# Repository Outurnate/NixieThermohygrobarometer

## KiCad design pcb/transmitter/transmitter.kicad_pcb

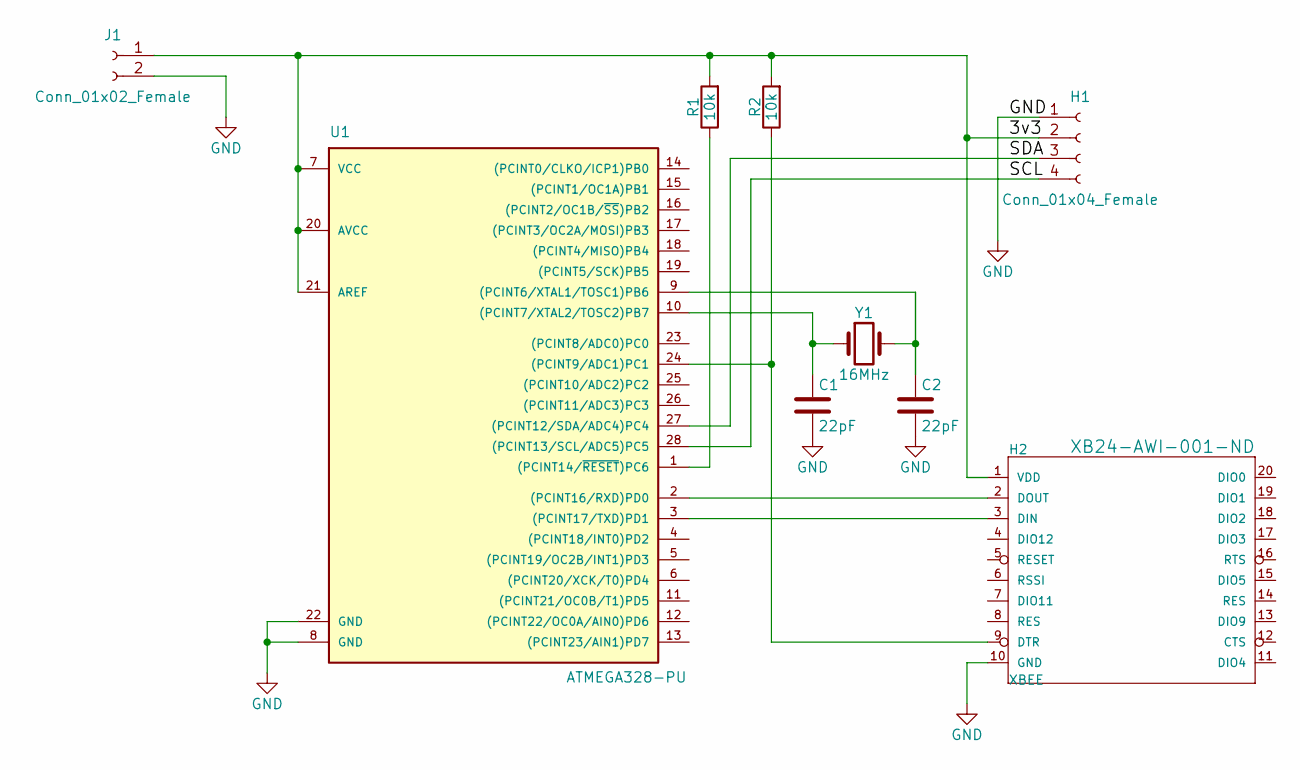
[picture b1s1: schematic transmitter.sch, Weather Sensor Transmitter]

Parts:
C1, C2: 22pF; C_Axial_L5.1mm_D3.1mm_P7.50mm_Horizontal
H1: Conn_01x04_Female; Socket_Strip_Straight_1x04_Pitch2.54mm
H2: XBEE
J1: Conn_01x02_Female; Socket_Strip_Straight_1x02_Pitch2.54mm
R1, R2: 10k; R_Axial_DIN0207_L6.3mm_D2.5mm_P7.62mm_Horizontal
U1: ATMEGA328-PU; DIP28
Y1: 16MHz; Crystal_HC49-U_Vertical

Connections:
/3v3: H1.2, H2.1 (VDD), J1.1, R1.2, R2.2, U1.7 (VCC), U1.20 (AVCC), U1.21 (AREF)
/SCL: H1.4, U1.28 ((PCINT13/SCL/ADC5)PC5)
/SDA: H1.3, U1.27 ((PCINT12/SDA/ADC4)PC4)
GND: C1.2, C2.2, H1.1, H2.10 (GND), J1.2, U1.8 (GND), U1.22 (GND)
unnamed: C1.1, U1.10 ((PCINT7/XTAL2/TOSC2)PB7), Y1.1
unnamed: C2.1, U1.9 ((PCINT6/XTAL1/TOSC1)PB6), Y1.2
unnamed: H2.2 (DOUT), U1.2 ((PCINT16/RXD)PD0)
unnamed: H2.3 (DIN), U1.3 ((PCINT17/TXD)PD1)
unnamed: H2.9 (DTR), R2.1, U1.24 ((PCINT9/ADC1)PC1)
unnamed: R1.1, U1.1 ((PCINT14/~RESET~)PC6)

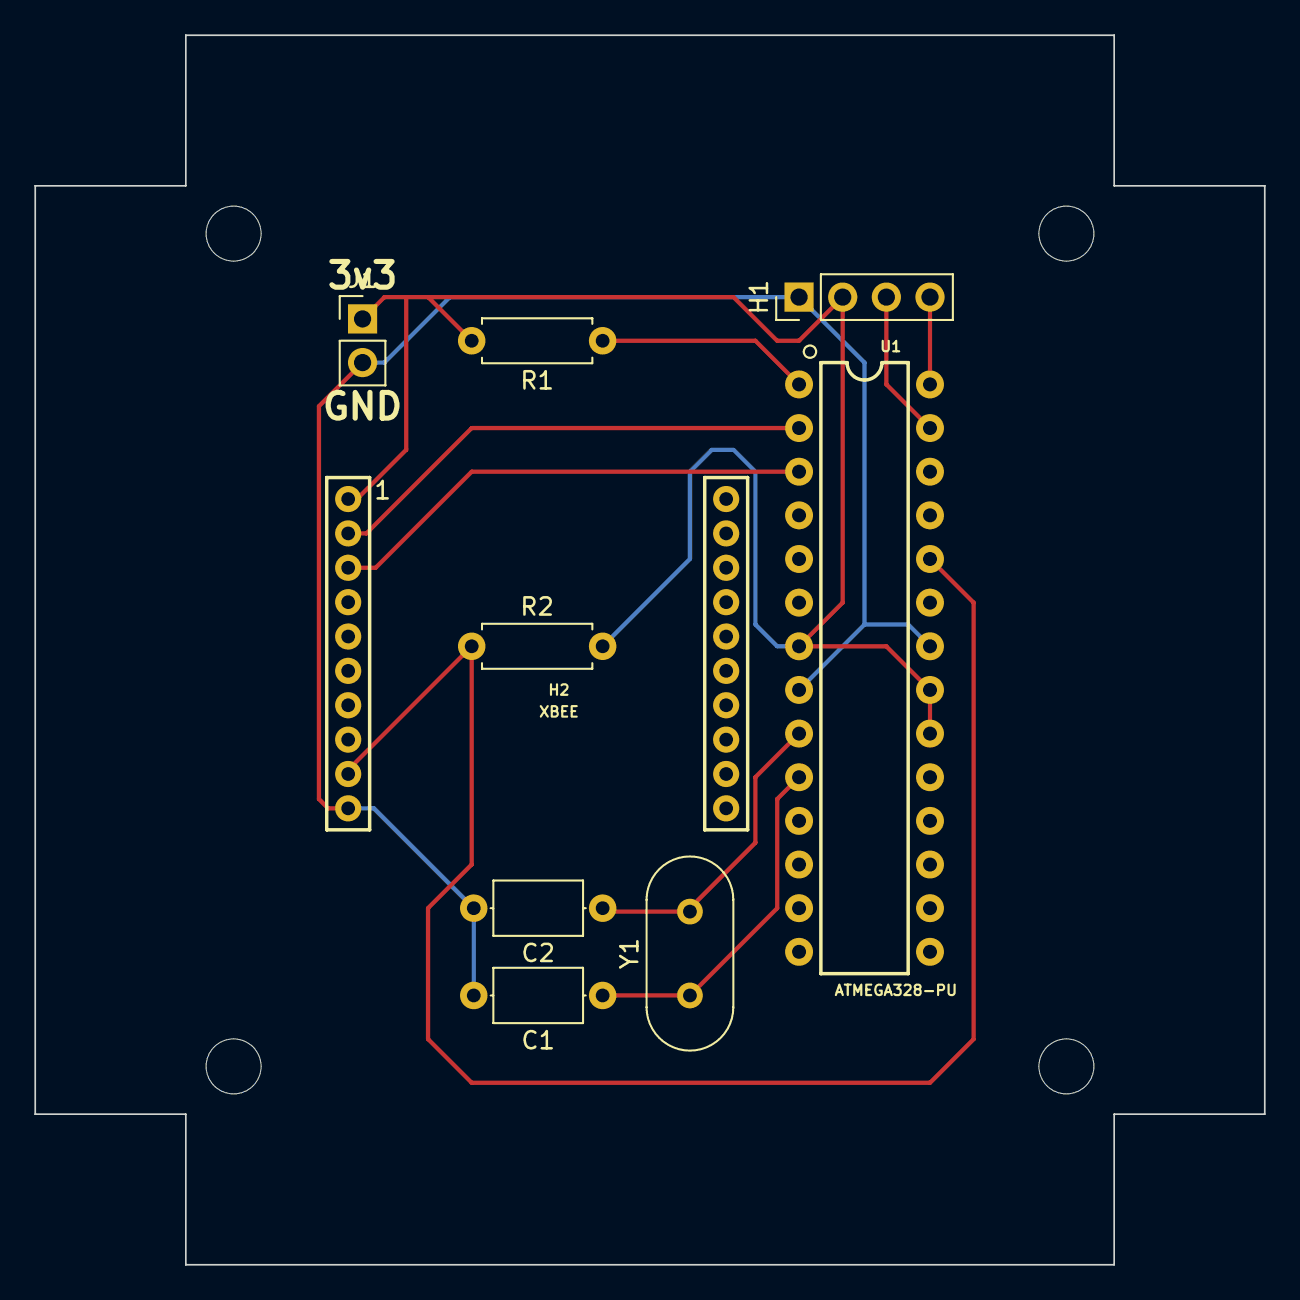
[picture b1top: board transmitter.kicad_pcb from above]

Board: 2 copper layers, 71.6 x 71.6 mm, 9 parts (0 on the bottom side), 10 nets.

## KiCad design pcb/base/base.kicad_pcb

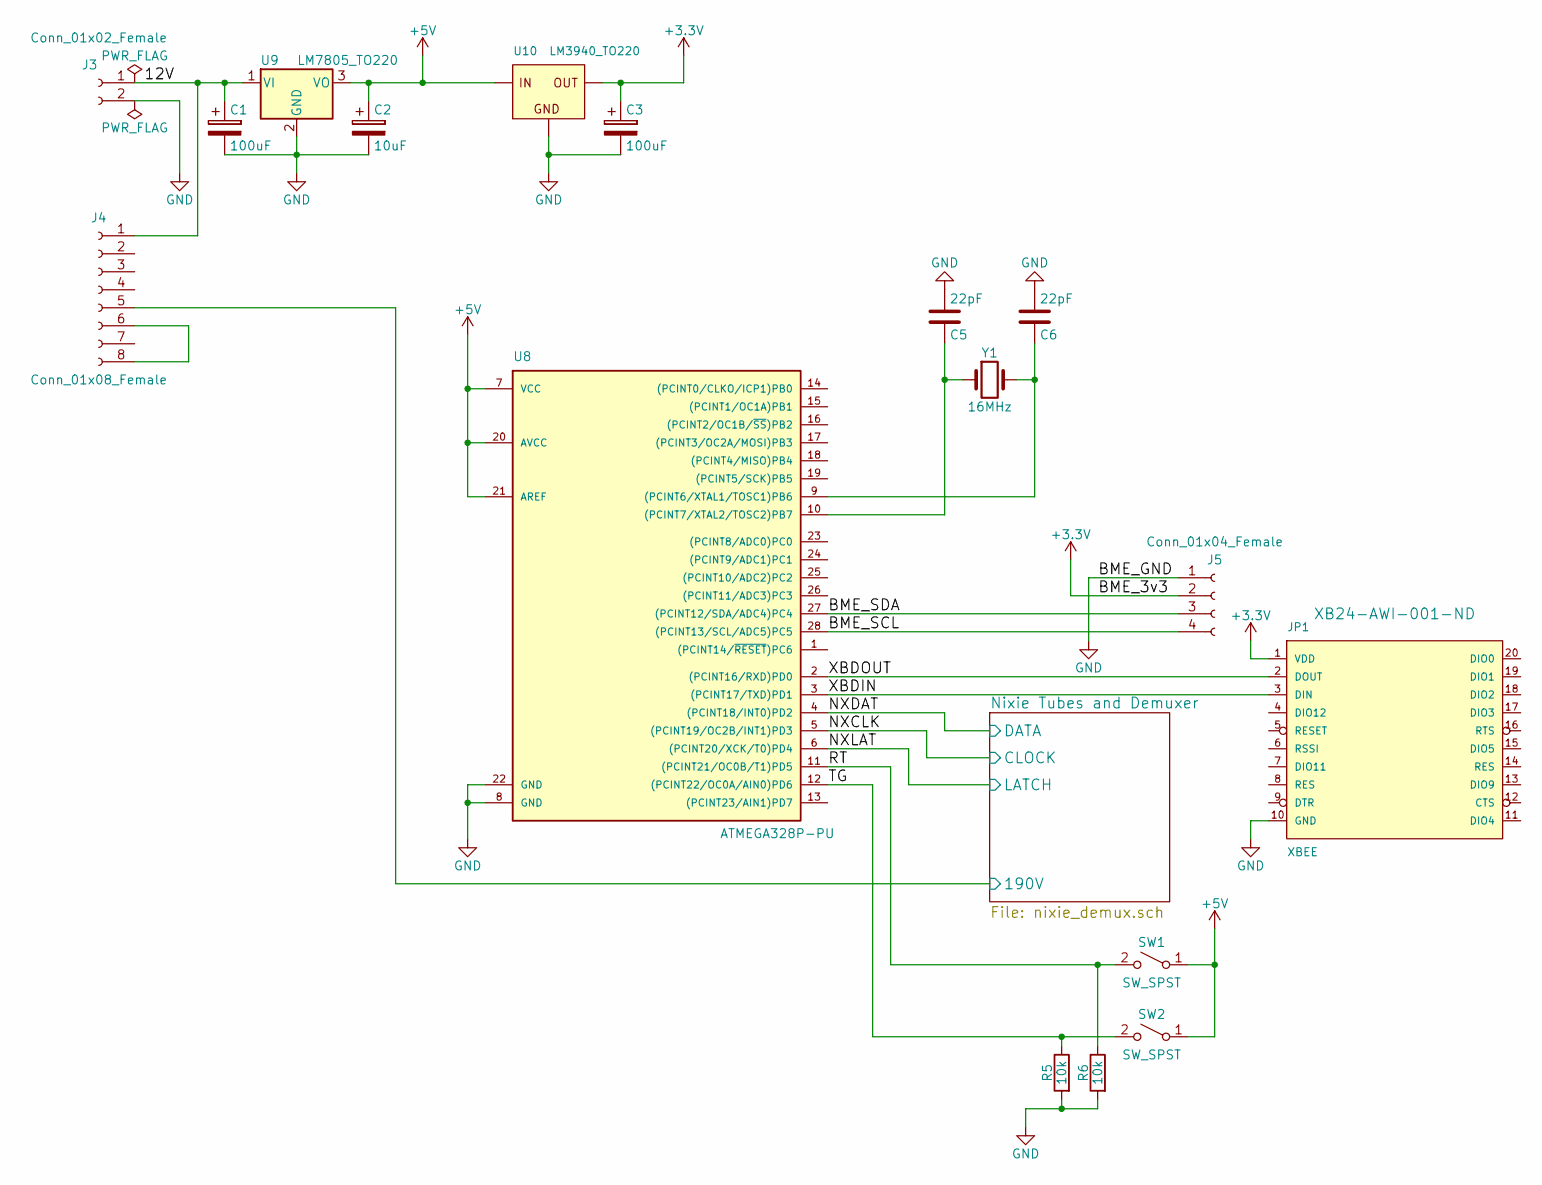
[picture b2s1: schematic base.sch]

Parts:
C1, C3: 100uF; CP_Radial_D6.3mm_P2.50mm
C2: 10uF; CP_Radial_D6.3mm_P2.50mm
C5, C6: 22pF; C_Disc_D4.3mm_W1.9mm_P5.00mm
J3: Conn_01x02_Female; Socket_Strip_Straight_1x02_Pitch2.54mm
J4: Conn_01x08_Female; Socket_Strip_Straight_1x08_Pitch2.54mm
J5: Conn_01x04_Female; Socket_Strip_Straight_1x04_Pitch2.54mm
JP1: XBEE
R5, R6: 10k; R_Axial_DIN0207_L6.3mm_D2.5mm_P7.62mm_Horizontal
SW1, SW2: SW_SPST; Pin_Header_Straight_1x02_Pitch2.54mm
U8: ATMEGA328P-PU; DIP28
U9: LM7805_TO220; TO-220-3_Vertical
U10: LM3940_TO220; TO-220-3_Vertical
Y1: 16MHz; Crystal_HC49-U_Vertical

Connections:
/12V: C1.1, J3.1, J4.1, U9.1 (VI)
/BME_SCL: J5.4, U8.28 ((PCINT13/SCL/ADC5)PC5)
/BME_SDA: J5.3, U8.27 ((PCINT12/SDA/ADC4)PC4)
/NXCLK: U8.5 ((PCINT19/OC2B/INT1)PD3); also elsewhere on the board
/NXDAT: U8.4 ((PCINT18/INT0)PD2); also elsewhere on the board
/NXLAT: U8.6 ((PCINT20/XCK/T0)PD4); also elsewhere on the board
/Nixie Tubes and Demuxer/190V: J4.5; also elsewhere on the board
/RT: R6.1, SW1.2 (B), U8.11 ((PCINT21/OC0B/T1)PD5)
/TG: R5.1, SW2.2 (B), U8.12 ((PCINT22/OC0A/AIN0)PD6)
/XBDIN: JP1.3 (DIN), U8.3 ((PCINT17/TXD)PD1)
/XBDOUT: JP1.2 (DOUT), U8.2 ((PCINT16/RXD)PD0)
GND: C1.2, C2.2, C3.2, C5.2, C6.2, J3.2, J5.1, JP1.10 (GND), R5.2, R6.2, U8.8 (GND), U8.22 (GND), U9.2 (GND), U10.2 (GND); also elsewhere on the board
unnamed: C5.1, U8.10 ((PCINT7/XTAL2/TOSC2)PB7), Y1.1
unnamed: C6.1, U8.9 ((PCINT6/XTAL1/TOSC1)PB6), Y1.2
unnamed: J4.6, J4.8

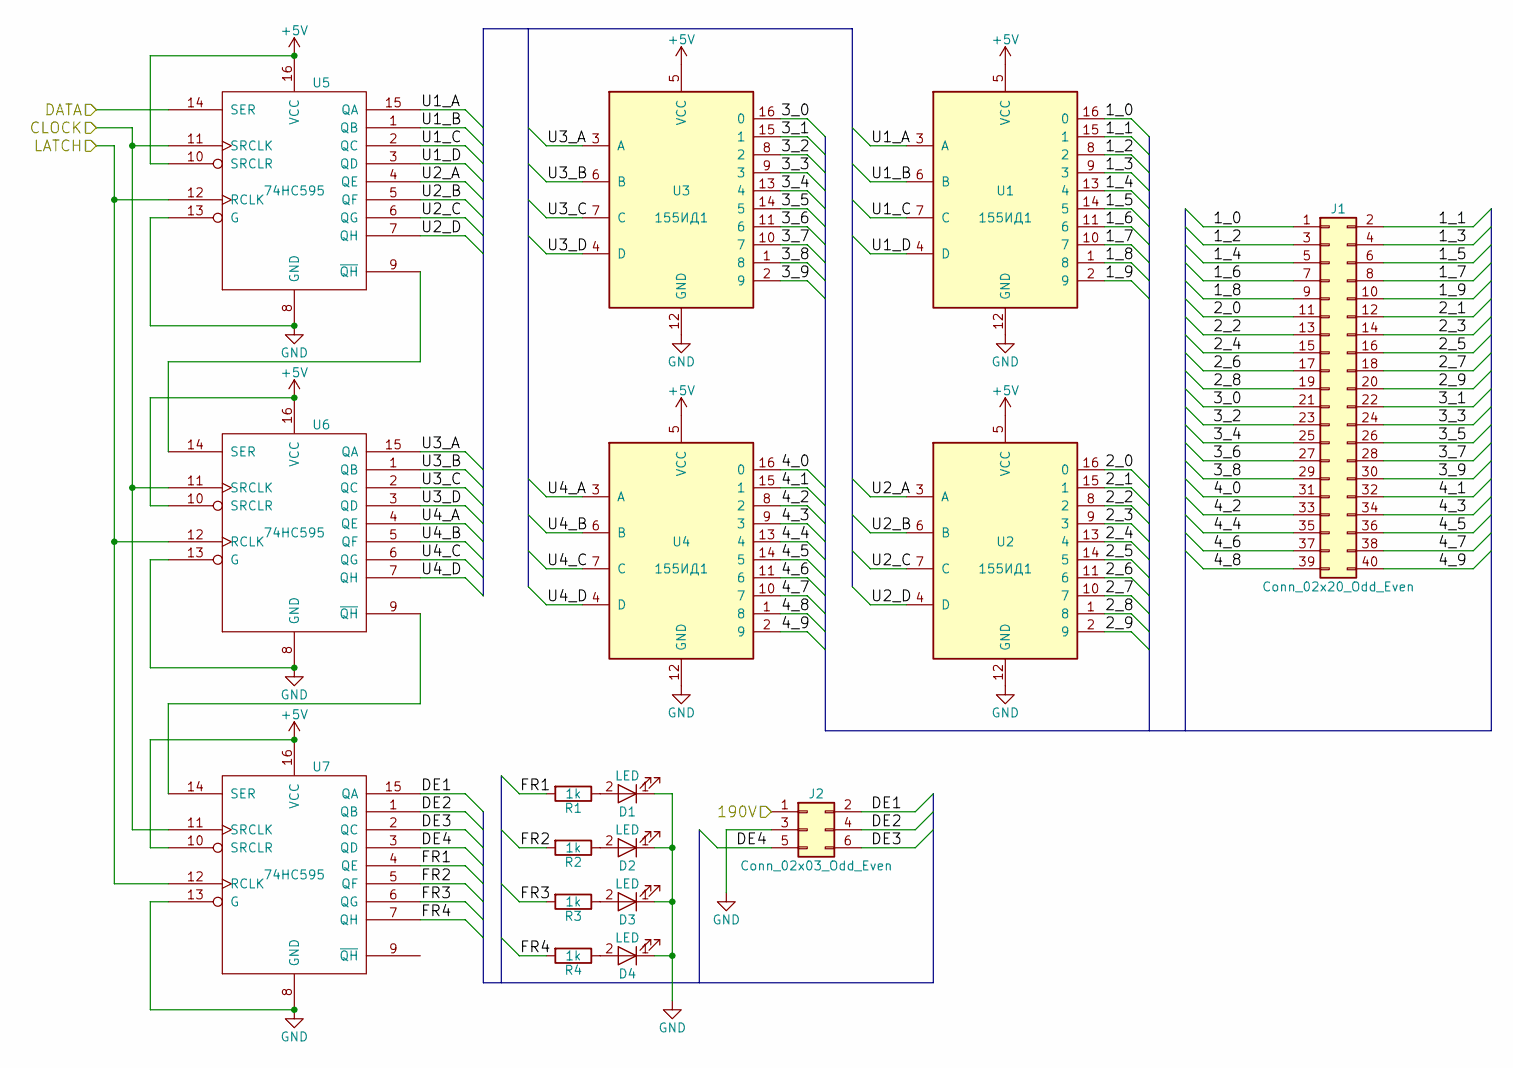
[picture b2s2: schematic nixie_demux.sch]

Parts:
D1, D2, D3, D4: LED; Socket_Strip_Straight_1x02_Pitch2.54mm
J1: Conn_02x20_Odd_Even; Pin_Header_Straight_2x20_Pitch2.54mm
J2: Conn_02x03_Odd_Even; Pin_Header_Straight_2x03_Pitch2.54mm
R1, R2, R3, R4: 1k; R_Axial_DIN0207_L6.3mm_D2.5mm_P7.62mm_Horizontal
U1, U2, U3, U4: 155ИД1; DIP-16_W7.62mm_Socket
U5, U6, U7: 74HC595; DIP-16_W7.62mm_Socket

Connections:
/NXCLK: U5.11 (SRCLK), U6.11 (SRCLK), U7.11 (SRCLK); also elsewhere on the board
/NXDAT: U5.14 (SER); also elsewhere on the board
/NXLAT: U5.12 (RCLK), U6.12 (RCLK), U7.12 (RCLK); also elsewhere on the board
/Nixie Tubes and Demuxer/1_0: J1.1, U1.16 (0)
/Nixie Tubes and Demuxer/1_1: J1.2, U1.15 (1)
/Nixie Tubes and Demuxer/1_2: J1.3, U1.8 (2)
/Nixie Tubes and Demuxer/1_3: J1.4, U1.9 (3)
/Nixie Tubes and Demuxer/1_4: J1.5, U1.13 (4)
/Nixie Tubes and Demuxer/1_5: J1.6, U1.14 (5)
/Nixie Tubes and Demuxer/1_6: J1.7, U1.11 (6)
/Nixie Tubes and Demuxer/1_7: J1.8, U1.10 (7)
/Nixie Tubes and Demuxer/1_8: J1.9, U1.1 (8)
/Nixie Tubes and Demuxer/1_9: J1.10, U1.2 (9)
/Nixie Tubes and Demuxer/2_0: J1.11, U2.16 (0)
/Nixie Tubes and Demuxer/2_1: J1.12, U2.15 (1)
/Nixie Tubes and Demuxer/2_2: J1.13, U2.8 (2)
/Nixie Tubes and Demuxer/2_3: J1.14, U2.9 (3)
/Nixie Tubes and Demuxer/2_4: J1.15, U2.13 (4)
/Nixie Tubes and Demuxer/2_5: J1.16, U2.14 (5)
/Nixie Tubes and Demuxer/2_6: J1.17, U2.11 (6)
/Nixie Tubes and Demuxer/2_7: J1.18, U2.10 (7)
/Nixie Tubes and Demuxer/2_8: J1.19, U2.1 (8)
/Nixie Tubes and Demuxer/2_9: J1.20, U2.2 (9)
/Nixie Tubes and Demuxer/3_0: J1.21, U3.16 (0)
/Nixie Tubes and Demuxer/3_1: J1.22, U3.15 (1)
/Nixie Tubes and Demuxer/3_2: J1.23, U3.8 (2)
/Nixie Tubes and Demuxer/3_3: J1.24, U3.9 (3)
/Nixie Tubes and Demuxer/3_4: J1.25, U3.13 (4)
/Nixie Tubes and Demuxer/3_5: J1.26, U3.14 (5)
/Nixie Tubes and Demuxer/3_6: J1.27, U3.11 (6)
/Nixie Tubes and Demuxer/3_7: J1.28, U3.10 (7)
/Nixie Tubes and Demuxer/3_8: J1.29, U3.1 (8)
/Nixie Tubes and Demuxer/3_9: J1.30, U3.2 (9)
/Nixie Tubes and Demuxer/4_0: J1.31, U4.16 (0)
/Nixie Tubes and Demuxer/4_1: J1.32, U4.15 (1)
/Nixie Tubes and Demuxer/4_2: J1.33, U4.8 (2)
/Nixie Tubes and Demuxer/4_3: J1.34, U4.9 (3)
/Nixie Tubes and Demuxer/4_4: J1.35, U4.13 (4)
/Nixie Tubes and Demuxer/4_5: J1.36, U4.14 (5)
/Nixie Tubes and Demuxer/4_6: J1.37, U4.11 (6)
/Nixie Tubes and Demuxer/4_7: J1.38, U4.10 (7)
/Nixie Tubes and Demuxer/4_8: J1.39, U4.1 (8)
/Nixie Tubes and Demuxer/4_9: J1.40, U4.2 (9)
/Nixie Tubes and Demuxer/190V: J2.1; also elsewhere on the board
/Nixie Tubes and Demuxer/DE1: J2.2, U7.15 (QA)
/Nixie Tubes and Demuxer/DE2: J2.4, U7.1 (QB)
/Nixie Tubes and Demuxer/DE3: J2.6, U7.2 (QC)
/Nixie Tubes and Demuxer/DE4: J2.5, U7.3 (QD)
/Nixie Tubes and Demuxer/FR1: R1.2, U7.4 (QE)
/Nixie Tubes and Demuxer/FR2: R2.2, U7.5 (QF)
/Nixie Tubes and Demuxer/FR3: R3.2, U7.6 (QG)
/Nixie Tubes and Demuxer/FR4: R4.2, U7.7 (QH)
/Nixie Tubes and Demuxer/U1_A: U1.3 (A), U5.15 (QA)
/Nixie Tubes and Demuxer/U1_B: U1.6 (B), U5.1 (QB)
/Nixie Tubes and Demuxer/U1_C: U1.7 (C), U5.2 (QC)
/Nixie Tubes and Demuxer/U1_D: U1.4 (D), U5.3 (QD)
/Nixie Tubes and Demuxer/U2_A: U2.3 (A), U5.4 (QE)
/Nixie Tubes and Demuxer/U2_B: U2.6 (B), U5.5 (QF)
/Nixie Tubes and Demuxer/U2_C: U2.7 (C), U5.6 (QG)
/Nixie Tubes and Demuxer/U2_D: U2.4 (D), U5.7 (QH)
/Nixie Tubes and Demuxer/U3_A: U3.3 (A), U6.15 (QA)
/Nixie Tubes and Demuxer/U3_B: U3.6 (B), U6.1 (QB)
/Nixie Tubes and Demuxer/U3_C: U3.7 (C), U6.2 (QC)
/Nixie Tubes and Demuxer/U3_D: U3.4 (D), U6.3 (QD)
/Nixie Tubes and Demuxer/U4_A: U4.3 (A), U6.4 (QE)
/Nixie Tubes and Demuxer/U4_B: U4.6 (B), U6.5 (QF)
/Nixie Tubes and Demuxer/U4_C: U4.7 (C), U6.6 (QG)
/Nixie Tubes and Demuxer/U4_D: U4.4 (D), U6.7 (QH)
GND: D1.1 (K), D2.1 (K), D3.1 (K), D4.1 (K), J2.3, U1.12 (GND), U2.12 (GND), U3.12 (GND), U4.12 (GND), U5.8 (GND), U5.13 (G), U6.8 (GND), U6.13 (G), U7.8 (GND), U7.13 (G); also elsewhere on the board
unnamed: D1.2 (A), R1.1
unnamed: D2.2 (A), R2.1
unnamed: D3.2 (A), R3.1
unnamed: D4.2 (A), R4.1
unnamed: U5.9 (~QH), U6.14 (SER)
unnamed: U6.9 (~QH), U7.14 (SER)

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
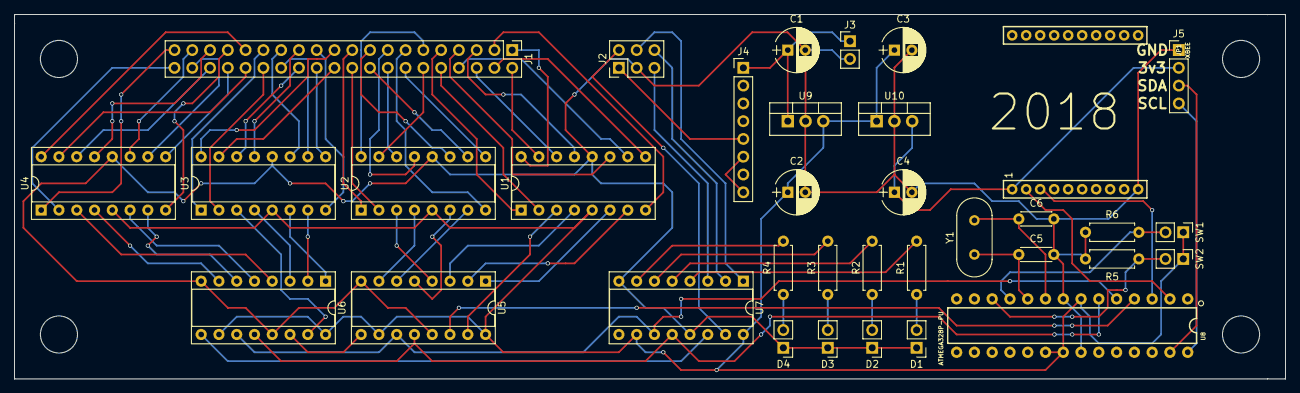
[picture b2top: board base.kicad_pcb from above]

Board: 2 copper layers, 181.6 x 52.1 mm, 35 parts (0 on the bottom side), 87 nets.

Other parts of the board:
C4: 10uF; CP_Radial_D6.3mm_P2.50mm

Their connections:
GND: C4.2; also elsewhere on the board

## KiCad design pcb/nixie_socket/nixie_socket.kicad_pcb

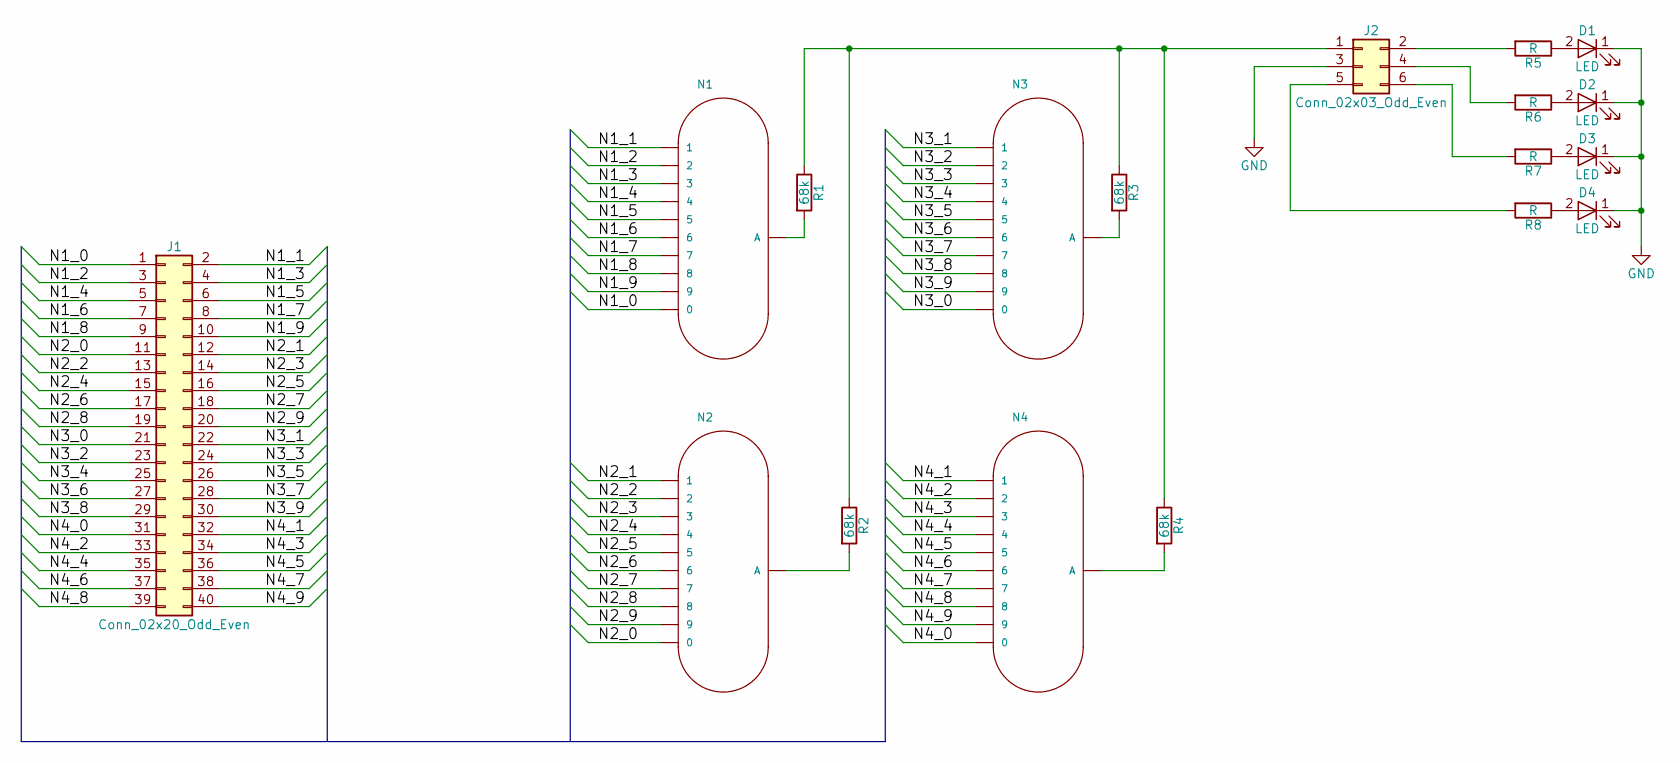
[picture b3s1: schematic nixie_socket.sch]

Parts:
D1, D2, D3, D4: LED; LED_D5.0mm
J1: Conn_02x20_Odd_Even; Pin_Header_Straight_2x20_Pitch2.54mm
J2: Conn_02x03_Odd_Even; Pin_Header_Straight_2x03_Pitch2.54mm
N1, N2, N3, N4: IN-8; nixies-us-IN-8
R1, R2, R3, R4: 68k; R_Axial_DIN0207_L6.3mm_D2.5mm_P7.62mm_Horizontal
R5, R6, R7, R8: R; R_Axial_DIN0207_L6.3mm_D2.5mm_P7.62mm_Horizontal

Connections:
/N1_0: J1.1, N1.0
/N1_1: J1.2, N1.1
/N1_2: J1.3, N1.2
/N1_3: J1.4, N1.3
/N1_4: J1.5, N1.4
/N1_5: J1.6, N1.5
/N1_6: J1.7, N1.6
/N1_7: J1.8, N1.7
/N1_8: J1.9, N1.8
/N1_9: J1.10, N1.9
/N2_0: J1.11, N2.0
/N2_1: J1.12, N2.1
/N2_2: J1.13, N2.2
/N2_3: J1.14, N2.3
/N2_4: J1.15, N2.4
/N2_5: J1.16, N2.5
/N2_6: J1.17, N2.6
/N2_7: J1.18, N2.7
/N2_8: J1.19, N2.8
/N2_9: J1.20, N2.9
/N3_0: J1.21, N3.0
/N3_1: J1.22, N3.1
/N3_2: J1.23, N3.2
/N3_3: J1.24, N3.3
/N3_4: J1.25, N3.4
/N3_5: J1.26, N3.5
/N3_6: J1.27, N3.6
/N3_7: J1.28, N3.7
/N3_8: J1.29, N3.8
/N3_9: J1.30, N3.9
/N4_0: J1.31, N4.0
/N4_1: J1.32, N4.1
/N4_2: J1.33, N4.2
/N4_3: J1.34, N4.3
/N4_4: J1.35, N4.4
/N4_5: J1.36, N4.5
/N4_6: J1.37, N4.6
/N4_7: J1.38, N4.7
/N4_8: J1.39, N4.8
/N4_9: J1.40, N4.9
GND: D1.1 (K), D2.1 (K), D3.1 (K), D4.1 (K), J2.3
unnamed: D1.2 (A), R5.1
unnamed: D2.2 (A), R6.1
unnamed: D3.2 (A), R7.1
unnamed: D4.2 (A), R8.1
unnamed: J2.1, R1.1, R2.1, R3.1, R4.1
unnamed: J2.2, R5.2
unnamed: J2.4, R6.2
unnamed: J2.5, R8.2
unnamed: J2.6, R7.2
unnamed: N1.A, R1.2
unnamed: N2.A, R2.2
unnamed: N3.A, R3.2
unnamed: N4.A, R4.2

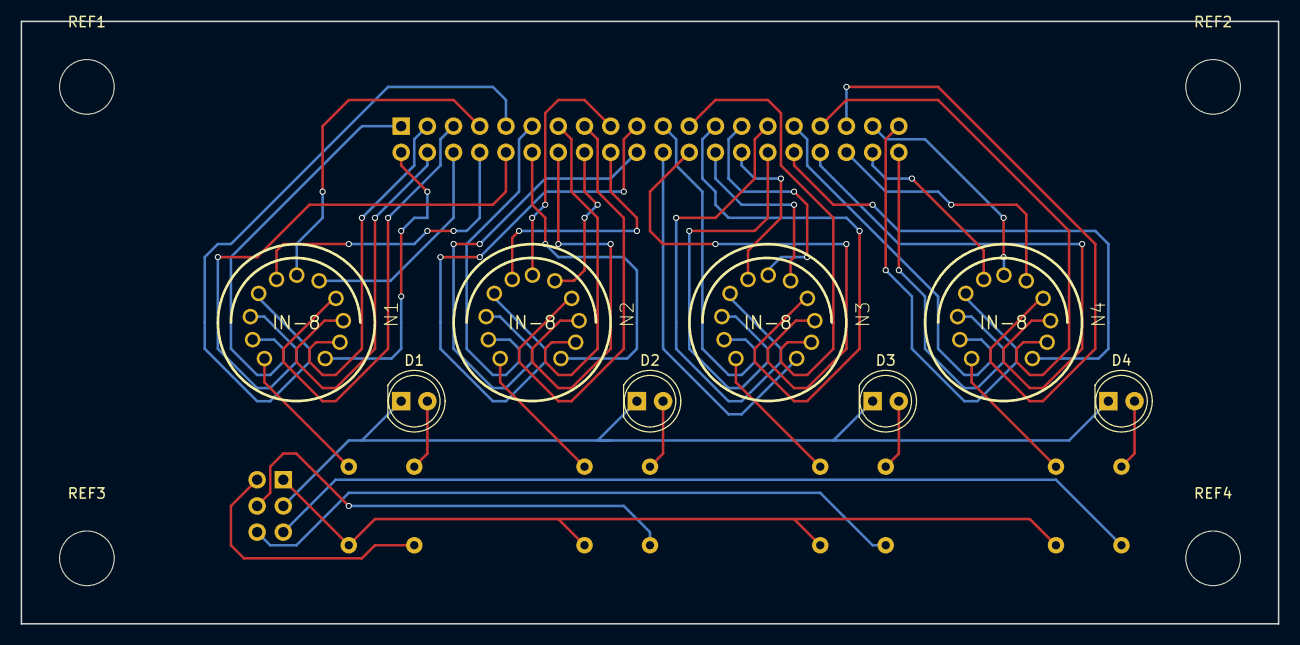
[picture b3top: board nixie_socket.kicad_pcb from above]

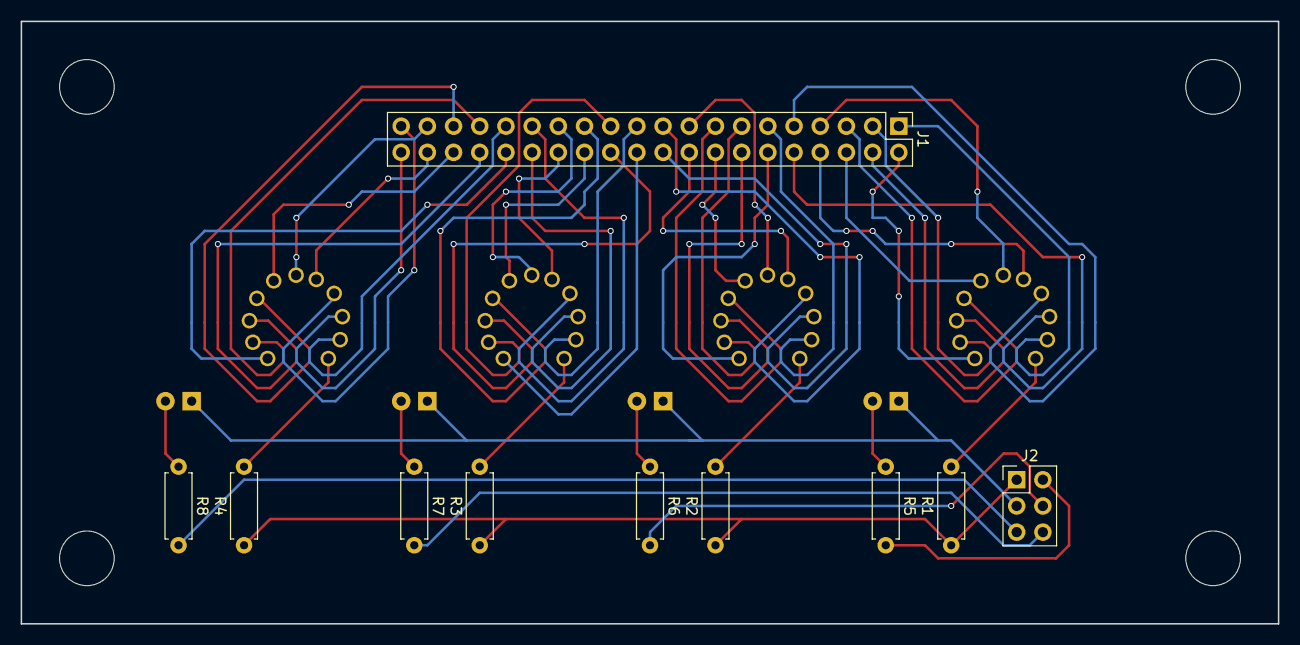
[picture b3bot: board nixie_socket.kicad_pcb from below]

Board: 2 copper layers, 121.9 x 58.4 mm, 22 parts (10 on the bottom side), 54 nets.

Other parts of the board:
REF1, REF2, REF3, REF4: MountingHole_5.3mm_M5

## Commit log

2018-09-03 Gotta license it
2018-09-08 adding upload scripts
